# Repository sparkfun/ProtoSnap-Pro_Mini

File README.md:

**_NOTE: This product has been retired from our catalog. This information is made available for those who are curious._**

ProtoSnap Pro-Mini
===================

[
*ProtoSnap Pro Mini (DEV-10889)*](https://www.sparkfun.com/products/10889)

The ProtoSnap is an Arduino-compatible development platform aimed at teach the basics of Arduino programming as efficiently as possible.

Repository Contents
-------------------
* **/Hardware** - All Eagle design files (.brd, .sch)
* **/Production** - Test bed files and production panel files

Product Versions
----------------
* [DEV-10889](https://www.sparkfun.com/products/10889)- Standard ProtoSnap Pro Mini
* [RTL-11053] (https://www.sparkfun.com/products/11053)- Retail version of ProtoSnap Pro Mini

License Information
-------------------
The hardware is released under [Creative Commons ShareAlike 4.0 International](https://creativecommons.org/licenses/by-sa/4.0/).
The code is beerware; if you see me (or any other SparkFun employee) at the local, and you've found our code helpful, please buy us a round!

Distributed as-is; no warranty is given.

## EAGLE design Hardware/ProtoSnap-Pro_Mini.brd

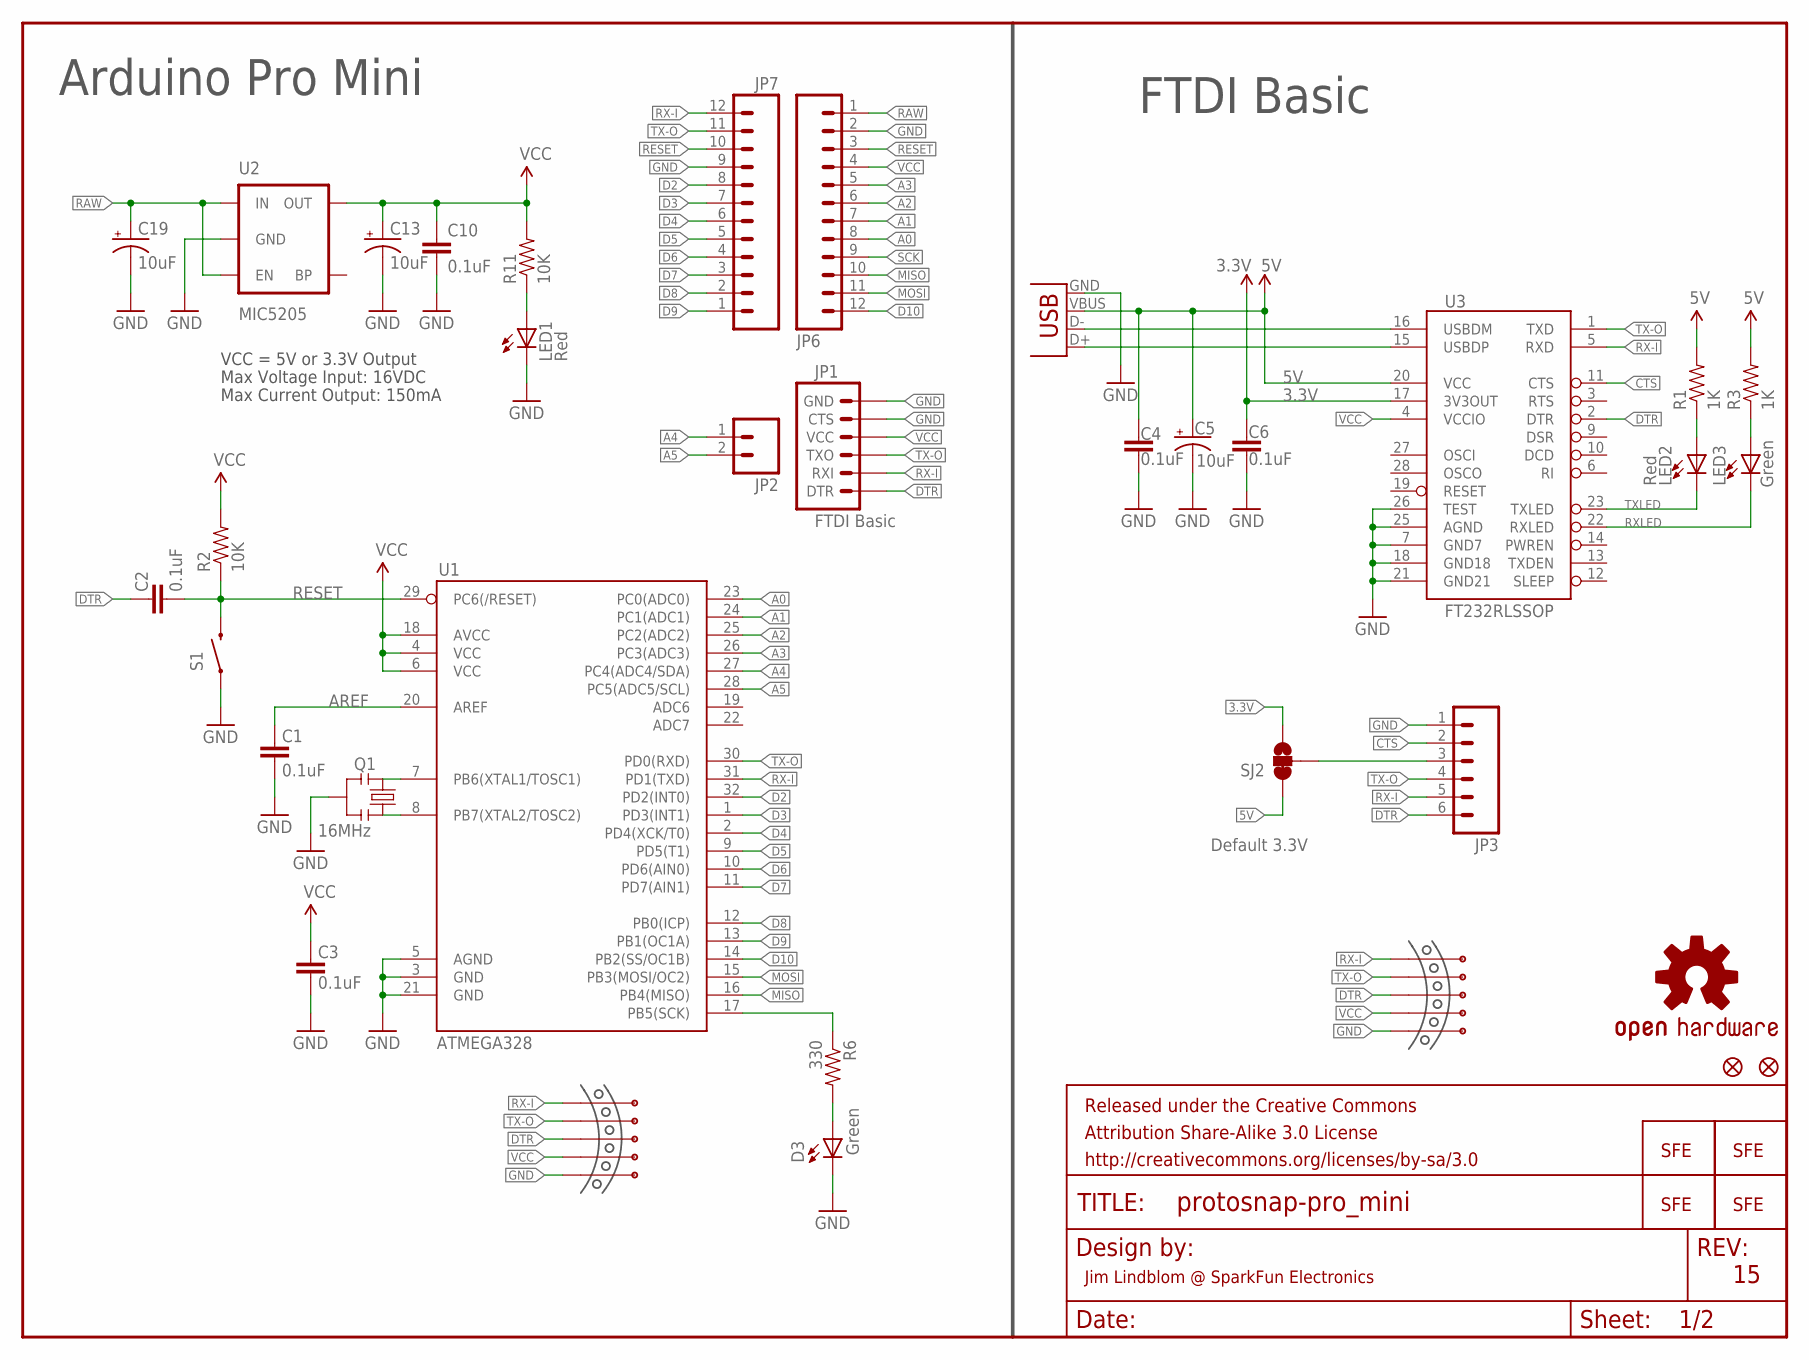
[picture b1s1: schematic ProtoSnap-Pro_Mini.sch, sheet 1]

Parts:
C1, C2, C3, C4, C6, C10: 0.1uF; 0603-CAP
C5, C13, C19: 10uF; EIA3216
D3: Green; 0603-LED-ALT1
FID1, FID2: FIDUCIAL1X2; FIDUCIAL-1X2
FRAME1: FRAME-LETTER; CREATIVE_COMMONS
JP1: FTDI Basic; 1X06
JP2: M02PTH; 1X02
JP3: M06SIP; 1X06
JP4: LOGO-SFENW2; SFE-NEW-WEB
JP6, JP7: M12PTH; 1X12
JP15, JP17: LOGO-SFESK; SFE-LOGO-FLAME
JP18: LOGO-SFENEW; SFE-NEW-WEBLOGO
LED1, LED2: Red; 0603-LED-ALT1
LED3: Green; 0603-LED-ALT1
LOGO1: OSHW-LOGOS; OSHW-LOGO-S
Q1: 16MHz; RESONATOR-SMD-1:1
R1, R3: 1K; 0603-RES
R2, R11: 10K; 0603-RES
R6: 330; 0603-RES
S1: SWITCH-MOMENTARY-2SMD-ALT01; TACTILE-SWITCH-SMD-ALT01
SJ2: SOLDERJUMPER_2WAYS; SJ_3
U1: ATMEGA328; TQFP32-08
U2: MIC5205; SOT23-5
U3: FT232RLSSOP; SSOP28DB
U$22, U$23: MOUSE-BITE-5
X2: USB-SMD-NS; USB-MINIB-NOSTOP

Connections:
3.3V: C6.1, SJ2.3, U3.17 (3V3OUT)
5V: C4.1, C5.A (+), R1.2, R3.2, SJ2.1, U3.20 (VCC), X2.VBUS
A0: JP6.8, U1.23 (PC0(ADC0)); also elsewhere on the board
A1: JP6.7, U1.24 (PC1(ADC1))
A2: JP6.6, U1.25 (PC2(ADC2))
A3: JP6.5, U1.26 (PC3(ADC3))
A4: JP2.1, U1.27 (PC4(ADC4/SDA))
A5: JP2.2, U1.28 (PC5(ADC5/SCL))
AREF: C1.2, U1.20 (AREF)
CTS: JP3.2, U3.11 (CTS)
D2: JP7.8, U1.32 (PD2(INT0)); also elsewhere on the board
D3: JP7.7, U1.1 (PD3(INT1)); also elsewhere on the board
D4: JP7.6, U1.2 (PD4(XCK/T0))
D5: JP7.5, U1.9 (PD5(T1)); also elsewhere on the board
D6: JP7.4, U1.10 (PD6(AIN0)); also elsewhere on the board
D7: JP7.3, U1.11 (PD7(AIN1)); also elsewhere on the board
D8: JP7.2, U1.12 (PB0(ICP))
D9: JP7.1, U1.13 (PB1(OC1A))
D10: JP6.12, U1.14 (PB2(SS/OC1B))
DTR: C2.2, JP1.1 (DTR), JP3.6, U3.2 (DTR), U$22.P$3, U$23.P$3
GND: C1.1, C3.1, C4.2, C5.C (-), C6.2, C10.2, C13.C (-), C19.C (-), D3.C, JP1.5 (CTS), JP1.6 (GND), JP3.1, JP6.2, JP7.9, LED1.C, Q1.2, S1.1, S1.2 (1), U1.3 (GND), U1.5 (AGND), U1.21 (GND), U2.2 (GND), U3.7 (GND7), U3.18 (GND18), U3.21 (GND21), U3.25 (AGND), U3.26 (TEST), U$22.P$5, U$23.P$5, X2.GND; also elsewhere on the board
MISO: JP6.10, U1.16 (PB4(MISO))
MOSI: JP6.11, U1.15 (PB3(MOSI/OC2))
unnamed: Q1.1, U1.8 (PB7(XTAL2/TOSC2))
unnamed: Q1.3, U1.7 (PB6(XTAL1/TOSC1))
unnamed: LED2.A, R1.1
unnamed: LED3.A, R3.1
unnamed: D3.A, R6.2
unnamed: LED1.A, R11.1
RAW: C19.A (+), JP6.1, U2.1 (IN), U2.3 (EN)
RESET: C2.1, JP6.3, JP7.10, R2.1, S1.3 (2), S1.4 (2), U1.29 (PC6(/RESET))
RX-I: JP1.2 (RXI), JP3.5, JP7.12, U1.31 (PD1(TXD)), U3.5 (RXD), U$22.P$1, U$23.P$1
RXLED: LED3.C, U3.22 (RXLED)
SCK: JP6.9, R6.1, U1.17 (PB5(SCK))
TX-O: JP1.3 (TXO), JP3.4, JP7.11, U1.30 (PD0(RXD)), U3.1 (TXD), U$22.P$2, U$23.P$2
TXLED: LED2.C, U3.23 (TXLED)
USB_D+: U3.15 (USBDP), X2.D+
USB_D-: U3.16 (USBDM), X2.D-
VCC: C3.2, C10.1, C13.A (+), JP1.4 (VCC), JP3.3, JP6.4, R2.2, R11.2, SJ2.2, U1.4 (VCC), U1.6 (VCC), U1.18 (AVCC), U2.5 (OUT), U3.4 (VCCIO), U$22.P$4, U$23.P$4; also elsewhere on the board

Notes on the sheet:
Max Voltage Input: 16VDC
Max Current Output: 150mA
VCC = 5V or 3.3V Output
Jim Lindblom @ SparkFun Electronics
Arduino Pro Mini
Default 3.3V
FTDI Basic

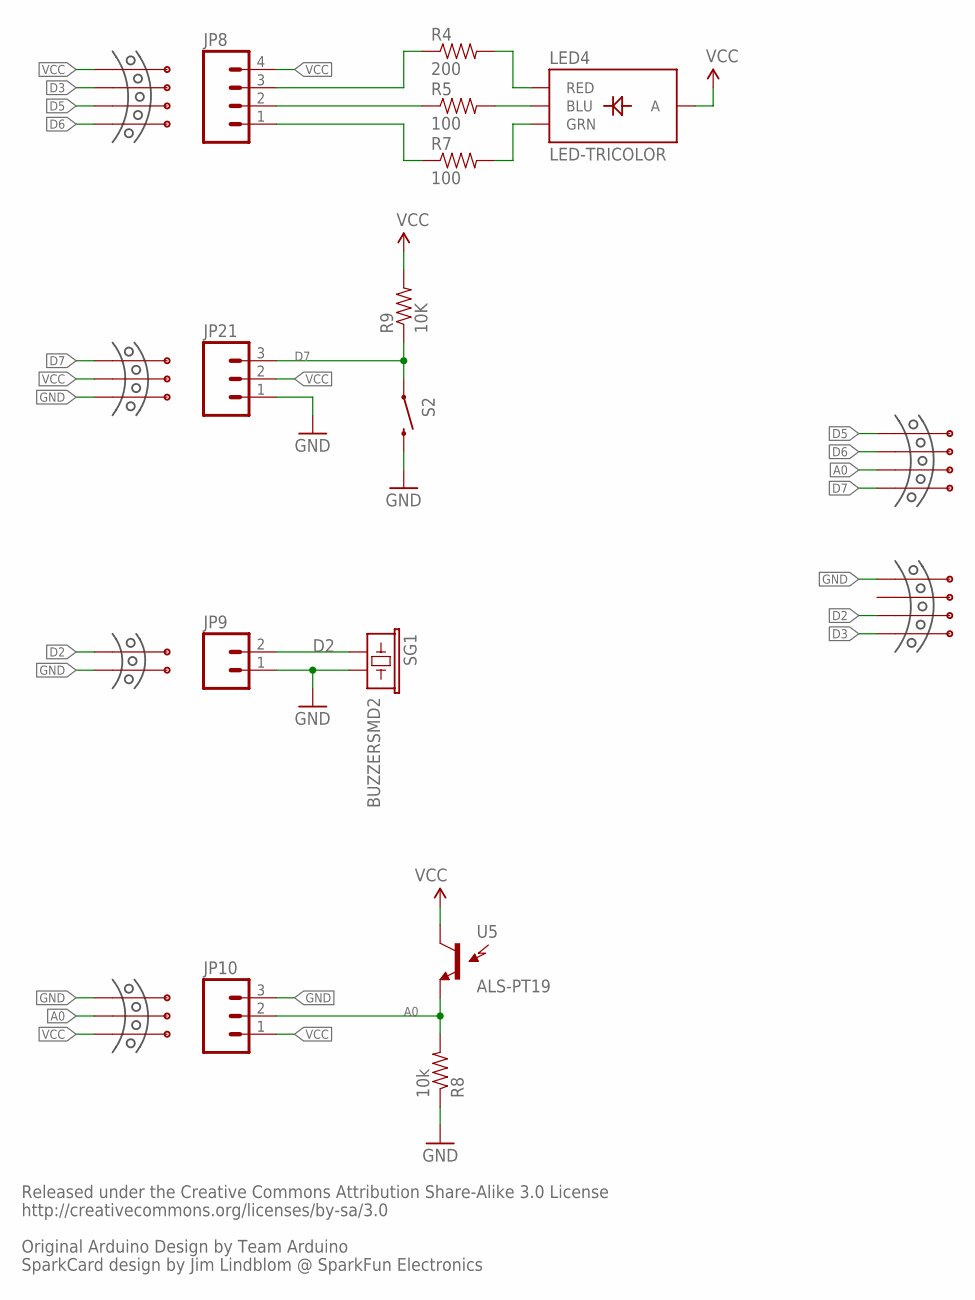
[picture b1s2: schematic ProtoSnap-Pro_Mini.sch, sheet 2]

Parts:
JP8: M04PTH; 1X04
JP9: M02PTH; 1X02
JP10, JP21: M03PTH; 1X03
LED4: LED-TRICOLOR; LED-TRICOLOR-SMD
R4: 200; 0603-RES
R5, R7: 100; 0603-RES
R8: 10k; 0603-RES
R9: 10K; 0603-RES
S2: SWITCH-MOMENTARY-2SMD-ALT01; TACTILE-SWITCH-SMD-ALT01
SG1: BUZZERSMD2; BUZZER-CCV
U5: ALS-PT19
U$2, U$9: MOUSE-BITE-3
U$7: MOUSE-BITE-2
U$8, U$13, U$14: MOUSE-BITE-4

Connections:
A0: JP10.2, R8.2, U5.E (E1), U$9.P$2, U$13.P$3; also elsewhere on the board
D2: JP9.2, SG1.+ (1), U$7.P$1, U$14.P$3; also elsewhere on the board
D3: JP8.3, R4.1, U$8.P$2, U$14.P$4; also elsewhere on the board
D5: JP8.1, R7.1, U$8.P$3, U$13.P$1; also elsewhere on the board
D6: JP8.2, R5.1, U$8.P$4, U$13.P$2; also elsewhere on the board
D7: JP21.3, R9.1, S2.1, S2.2 (1), U$2.P$3, U$13.P$4; also elsewhere on the board
GND: JP9.1, JP10.3, JP21.1, R8.1, S2.3 (2), S2.4 (2), SG1.- (2), U$2.P$1, U$7.P$2, U$9.P$3, U$14.P$1; also elsewhere on the board
unnamed: LED4.R (RED), R4.2
unnamed: LED4.B (BLU), R5.2
unnamed: LED4.G (GRN), R7.2
VCC: JP8.4, JP10.1, JP21.2, LED4.A, R9.2, U5.C (C1), U$2.P$2, U$8.P$1, U$9.P$1; also elsewhere on the board

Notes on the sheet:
Released under the Creative Commons Attribution Share-Alike 3.0 License
http://creativecommons.org/licenses/by-sa/3.0
Original Arduino Design by Team Arduino
SparkCard design by Jim Lindblom @ SparkFun Electronics

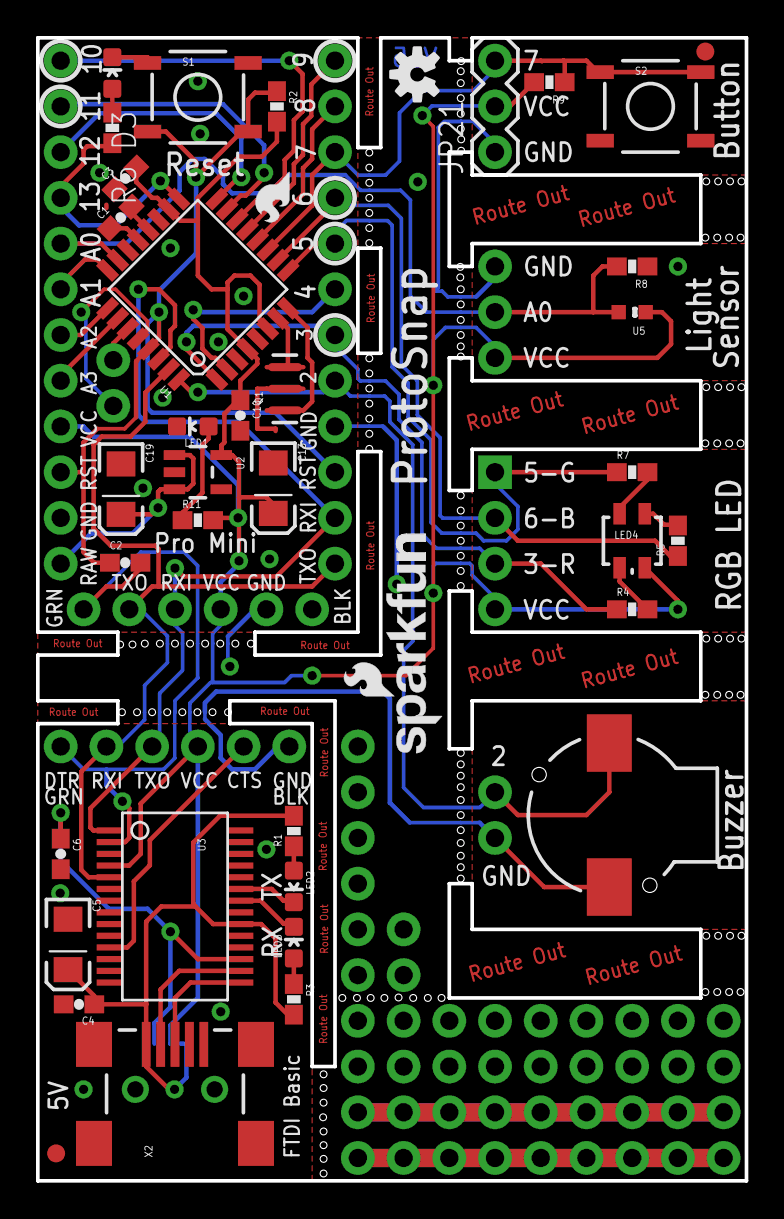
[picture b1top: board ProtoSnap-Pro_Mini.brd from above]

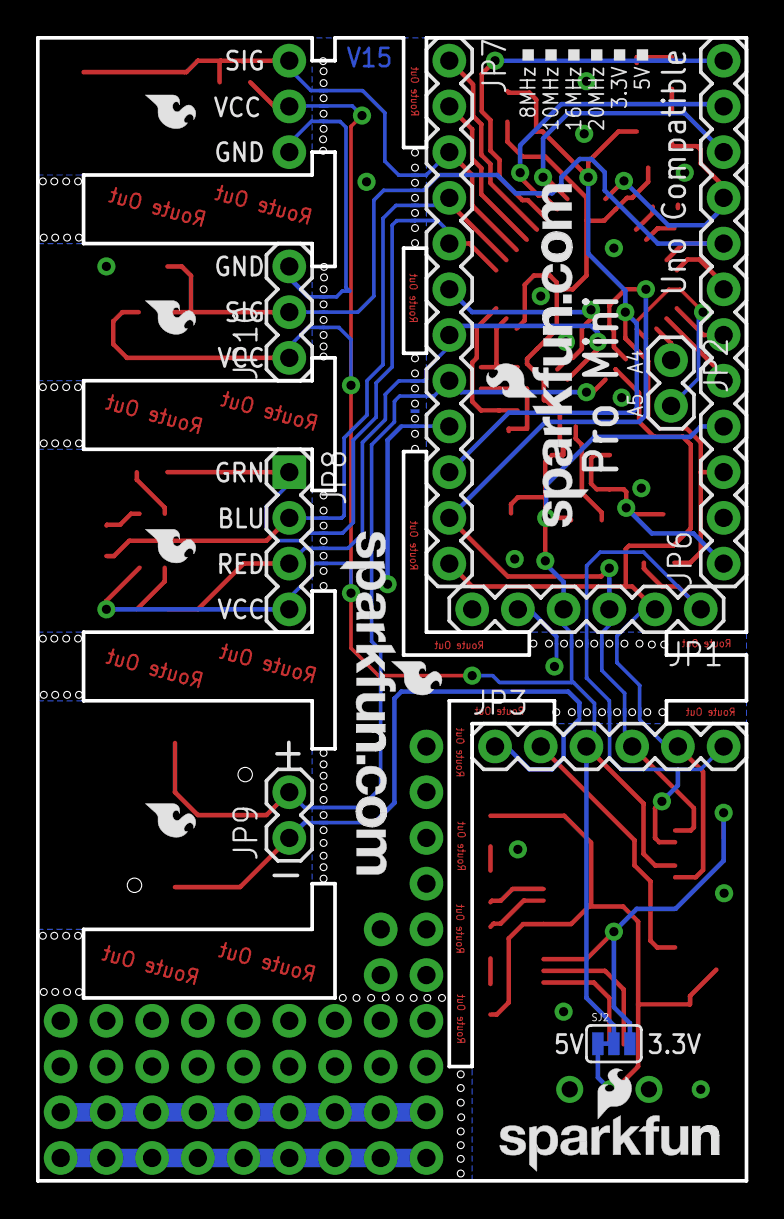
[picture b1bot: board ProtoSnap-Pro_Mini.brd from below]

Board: 2 copper layers, 39.4 x 63.5 mm, 66 parts (17 on the bottom side), 42 nets.

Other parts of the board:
JP5, JP11, JP13, JP14: LOGO-SFESK; SFE-LOGO-FLAME
JP12: LOGO-SFENW2; SFE-NEW-WEB
U$1: LOGO-SFESK; SFE-LOGO-FLAME
U$11: LOGO-SFENEW; SFE-NEW-WEBLOGO

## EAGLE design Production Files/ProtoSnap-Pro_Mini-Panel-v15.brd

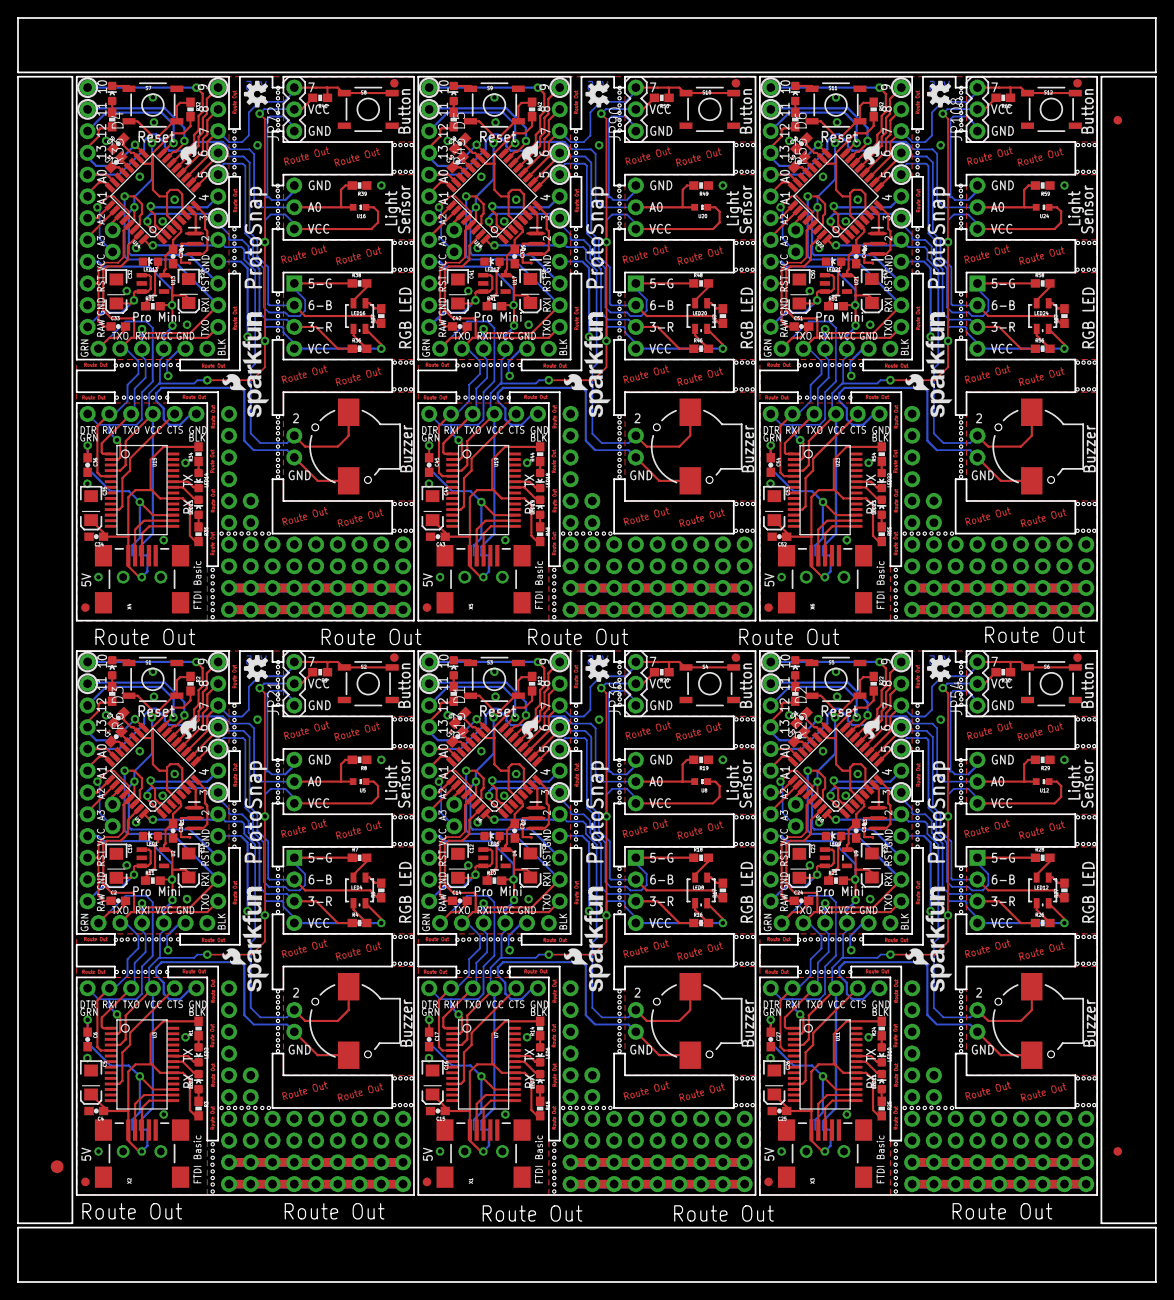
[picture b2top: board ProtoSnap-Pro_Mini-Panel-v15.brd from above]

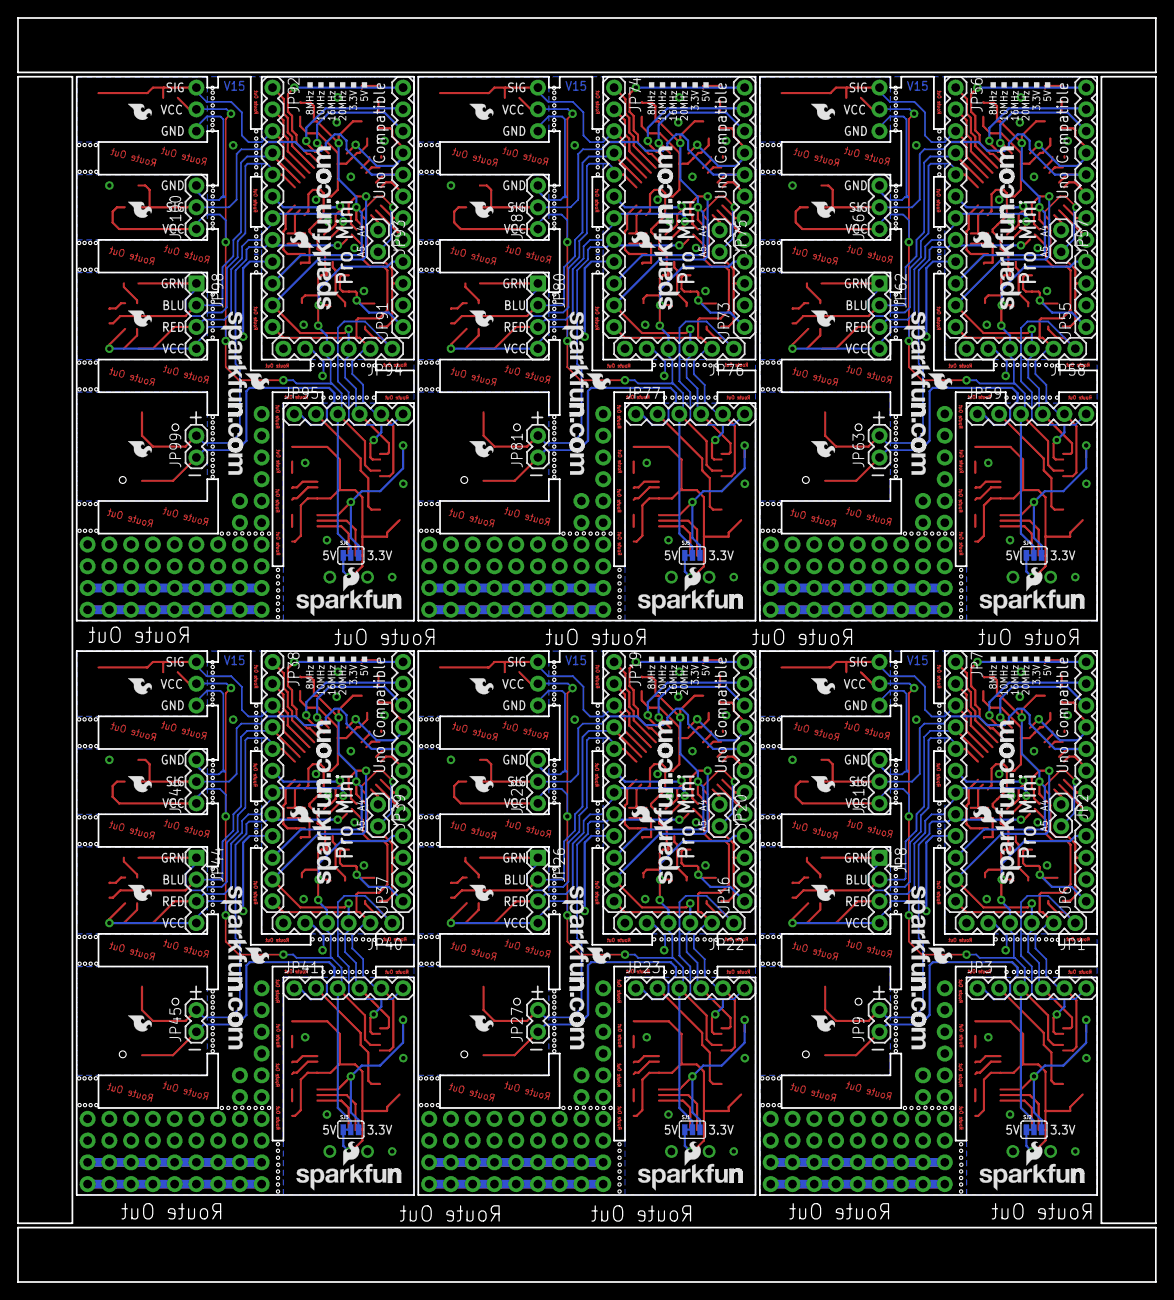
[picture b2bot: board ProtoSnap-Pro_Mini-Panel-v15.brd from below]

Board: 2 copper layers, 132.8 x 147.6 mm, 393 parts (102 on the bottom side), 252 nets.

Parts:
C1, C2, C3, C4, C6, C7, C9, C10, C11, C14, C15, C17, C18, C21, C22, C24, C25, C27, C28, C30, C31, C33, C34, C36, C37, C39, C40, C42, C43, C45, C46, C48, C49, C51, C52, C54: 0.1uF; 0603-CAP
C5, C8, C12, C13, C16, C19, C20, C23, C26, C29, C32, C35, C38, C41, C44, C47, C50, C53: 10uF; EIA3216
D1, D2, D3, D4, D5, D6: Green; 0603-LED-ALT1
E$1: FIDUCIAL-1.5X3
E$3, E$4: FIDUCIAL-1X2
FID1, FID2, FID3, FID4, FID5, FID6, FID7, FID8, FID9, FID10, FID11, FID12: FIDUCIAL1X2; FIDUCIAL-1X2
JP1, JP22, JP40, JP58, JP76, JP94: FTDI Basic; 1X06
JP2, JP9, JP20, JP27, JP39, JP45, JP57, JP63, JP75, JP81, JP93, JP99: 1X02
JP3, JP23, JP41, JP59, JP77, JP95: 1X06
JP4, JP12, JP24, JP33, JP42, JP51, JP60, JP69, JP78, JP87, JP96, JP105: LOGO-SFENW2; SFE-NEW-WEB
JP5, JP11, JP13, JP14, JP15, JP17, JP25, JP29, JP30, JP31, JP32, JP34, JP43, JP47, JP48, JP49, JP50, JP52, JP61, JP65, JP66, JP67, JP68, JP70, JP79, JP83, JP84, JP85, JP86, JP88, JP97, JP101, JP102, JP103, JP104, JP106: LOGO-SFESK; SFE-LOGO-FLAME
JP6, JP7, JP16, JP19, JP37, JP38, JP55, JP56, JP73, JP74, JP91, JP92: 1X12
JP8, JP26, JP44, JP62, JP80, JP98: 1X04
JP10, JP21, JP28, JP36, JP46, JP54, JP64, JP72, JP82, JP90, JP100, JP108: 1X03
JP18, JP35, JP53, JP71, JP89, JP107: LOGO-SFENEW; SFE-NEW-WEBLOGO
LED1, LED2, LED5, LED6, LED9, LED10, LED13, LED14, LED17, LED18, LED21, LED22: Red; 0603-LED-ALT1
LED3, LED7, LED11, LED15, LED19, LED23: Green; 0603-LED-ALT1
LED4, LED8, LED12, LED16, LED20, LED24: LED-TRICOLOR; LED-TRICOLOR-SMD
LOGO1, LOGO2, LOGO3, LOGO4, LOGO5, LOGO6: OSHW-LOGOS; OSHW-LOGO-S
Q1, Q2, Q3, Q4, Q5, Q6: 16MHz; RESONATOR-SMD-1:1
R1, R3, R14, R15, R24, R25, R34, R35, R44, R45, R54, R55: 1K; 0603-RES
R2, R9, R10, R11, R12, R20, R21, R22, R30, R31, R32, R40, R41, R42, R50, R51, R52, R60: 10K; 0603-RES
R4, R16, R26, R36, R46, R56: 200; 0603-RES
R5, R7, R17, R18, R27, R28, R37, R38, R47, R48, R57, R58: 100; 0603-RES
R6, R13, R23, R33, R43, R53: 330; 0603-RES
R8, R19, R29, R39, R49, R59: 10k; 0603-RES
S1, S2, S3, S4, S5, S6, S7, S8, S9, S10, S11, S12: TACTILE-SWITCH-SMD-ALT01
SG1, SG2, SG3, SG4, SG5, SG6: BUZZERSMD2; BUZZER-CCV
SJ1, SJ2, SJ3, SJ4, SJ5, SJ6: SJ_3
U1, U6, U10, U14, U18, U22: ATMEGA328; TQFP32-08
U2, U4, U9, U13, U17, U21: MIC5205; SOT23-5
U3, U7, U11, U15, U19, U23: FT232RLSSOP; SSOP28DB
U5, U8, U12, U16, U20, U24: ALS-PT19
U$1, U$4, U$20, U$32, U$42, U$52: LOGO-SFESK; SFE-LOGO-FLAME
U$2, U$9, U$16, U$18, U$28, U$30, U$38, U$40, U$48, U$50, U$58, U$60: MOUSE-BITE-3
U$3, U$11, U$19, U$31, U$41, U$51: LOGO-SFENEW; SFE-NEW-WEBLOGO
U$5, U$7, U$21, U$33, U$43, U$53: MOUSE-BITE-2
U$6, U$10, U$22, U$23, U$24, U$25, U$34, U$35, U$44, U$45, U$54, U$55: MOUSE-BITE-5
U$8, U$12, U$13, U$14, U$15, U$17, U$26, U$27, U$29, U$36, U$37, U$39, U$46, U$47, U$49, U$56, U$57, U$59: MOUSE-BITE-4
X1, X2, X3, X4, X5, X6: USB-SMD-NS; USB-MINIB-NOSTOP

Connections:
3.3V: C6.1, SJ2.3, U3.17
3.3V1: C17.1, SJ1.3, U7.17
3.3V2: C27.1, SJ3.3, U11.17
3.3V3: C36.1, SJ4.3, U15.17
3.3V4: C45.1, SJ5.3, U19.17
3.3V5: C54.1, SJ6.3, U23.17
5V: C4.1, C5.A, R1.2, R3.2, SJ2.1, U3.20, X2.VBUS
5V1: C15.1, C16.A, R14.2, R15.2, SJ1.1, U7.20, X1.VBUS
5V2: C25.1, C26.A, R24.2, R25.2, SJ3.1, U11.20, X3.VBUS
5V3: C34.1, C35.A, R34.2, R35.2, SJ4.1, U15.20, X4.VBUS
5V4: C43.1, C44.A, R44.2, R45.2, SJ5.1, U19.20, X5.VBUS
5V5: C52.1, C53.A, R54.2, R55.2, SJ6.1, U23.20, X6.VBUS
A0: JP6.8, JP10.2, R8.2, U1.23, U5.E, U$9.P$2, U$13.P$3
A1: JP6.7, U1.24
A2: JP6.6, U1.25
A3: JP6.5, U1.26
A4: JP2.1, U1.27
A5: JP2.2, U1.28
A6: JP20.2, U6.28
A7: JP20.1, U6.27
A8: JP16.5, U6.26
A9: JP16.6, U6.25
A10: JP16.7, U6.24
A11: JP16.8, JP28.2, R19.2, U6.23, U8.E, U$15.P$3, U$16.P$2
A12: JP39.2, U10.28
A13: JP39.1, U10.27
A14: JP37.5, U10.26
A15: JP37.6, U10.25
A16: JP37.7, U10.24
A17: JP37.8, JP46.2, R29.2, U10.23, U12.E, U$27.P$3, U$28.P$2
A18: JP57.2, U14.28
A19: JP57.1, U14.27
A20: JP55.5, U14.26
A21: JP55.6, U14.25
A22: JP55.7, U14.24
A23: JP55.8, JP64.2, R39.2, U14.23, U16.E, U$37.P$3, U$38.P$2
A24: JP75.2, U18.28
A25: JP75.1, U18.27
A26: JP73.5, U18.26
A27: JP73.6, U18.25
A28: JP73.7, U18.24
A29: JP73.8, JP82.2, R49.2, U18.23, U20.E, U$47.P$3, U$48.P$2
A30: JP93.2, U22.28
A31: JP93.1, U22.27
A32: JP91.5, U22.26
A33: JP91.6, U22.25
A34: JP91.7, U22.24
A35: JP91.8, JP100.2, R59.2, U22.23, U24.E, U$57.P$3, U$58.P$2
AREF: C1.2, U1.20
AREF1: C11.2, U6.20
AREF2: C22.2, U10.20
AREF3: C31.2, U14.20
AREF4: C40.2, U18.20
AREF5: C49.2, U22.20
CTS: JP3.2, U3.11
CTS1: JP23.2, U7.11
CTS2: JP41.2, U11.11
CTS3: JP59.2, U15.11
CTS4: JP77.2, U19.11
CTS5: JP95.2, U23.11
D1: JP19.1, U6.13
D2: JP7.8, JP9.2, SG1.+, U1.32, U$7.P$1, U$14.P$3
D3: JP7.7, JP8.3, R4.1, U1.1, U$8.P$2, U$14.P$4
D4: JP7.6, U1.2
D5: JP7.5, JP8.1, R7.1, U1.9, U$8.P$3, U$13.P$1
D6: JP7.4, JP8.2, R5.1, U1.10, U$8.P$4, U$13.P$2
D7: JP7.3, JP21.3, R9.1, S2.1, S2.2, U1.11, U$2.P$3, U$13.P$4
D8: JP7.2, U1.12
D9: JP7.1, U1.13
D10: JP6.12, U1.14
D11: JP19.2, U6.12
D12: JP19.8, JP27.2, SG2.+, U6.32, U$5.P$1, U$17.P$3
D13: JP19.7, JP26.3, R16.1, U6.1, U$12.P$2, U$17.P$4
D14: JP19.6, U6.2
D15: JP19.5, JP26.1, R18.1, U6.9, U$12.P$3, U$15.P$1
D16: JP19.4, JP26.2, R17.1, U6.10, U$12.P$4, U$15.P$2
D17: JP19.3, JP36.3, R20.1, S4.1, S4.2, U6.11, U$15.P$4, U$18.P$3
D18: JP16.12, U6.14
D19: JP38.1, U10.13
D20: JP38.2, U10.12
D21: JP38.8, JP45.2, SG3.+, U10.32, U$21.P$1, U$29.P$3
D22: JP38.7, JP44.3, R26.1, U10.1, U$26.P$2, U$29.P$4
D23: JP38.6, U10.2
D24: JP38.5, JP44.1, R28.1, U10.9, U$26.P$3, U$27.P$1
D25: JP38.4, JP44.2, R27.1, U10.10, U$26.P$4, U$27.P$2
D26: JP38.3, JP54.3, R30.1, S6.1, S6.2, U10.11, U$27.P$4, U$30.P$3
D27: JP37.12, U10.14
D28: JP56.1, U14.13
D29: JP56.2, U14.12
D30: JP56.8, JP63.2, SG4.+, U14.32, U$33.P$1, U$39.P$3
D31: JP56.7, JP62.3, R36.1, U14.1, U$36.P$2, U$39.P$4
D32: JP56.6, U14.2
D33: JP56.5, JP62.1, R38.1, U14.9, U$36.P$3, U$37.P$1
D34: JP56.4, JP62.2, R37.1, U14.10, U$36.P$4, U$37.P$2
D35: JP56.3, JP72.3, R40.1, S8.1, S8.2, U14.11, U$37.P$4, U$40.P$3
D36: JP55.12, U14.14
D37: JP74.1, U18.13
D38: JP74.2, U18.12
D39: JP74.8, JP81.2, SG5.+, U18.32, U$43.P$1, U$49.P$3
D40: JP74.7, JP80.3, R46.1, U18.1, U$46.P$2, U$49.P$4
D41: JP74.6, U18.2
D42: JP74.5, JP80.1, R48.1, U18.9, U$46.P$3, U$47.P$1
D43: JP74.4, JP80.2, R47.1, U18.10, U$46.P$4, U$47.P$2
D44: JP74.3, JP90.3, R50.1, S10.1, S10.2, U18.11, U$47.P$4, U$50.P$3
D45: JP73.12, U18.14
D46: JP92.1, U22.13
D47: JP92.2, U22.12
D48: JP92.8, JP99.2, SG6.+, U22.32, U$53.P$1, U$59.P$3
D49: JP92.7, JP98.3, R56.1, U22.1, U$56.P$2, U$59.P$4
D50: JP92.6, U22.2
D51: JP92.5, JP98.1, R58.1, U22.9, U$56.P$3, U$57.P$1
D52: JP92.4, JP98.2, R57.1, U22.10, U$56.P$4, U$57.P$2
D53: JP92.3, JP108.3, R60.1, S12.1, S12.2, U22.11, U$57.P$4, U$60.P$3
D54: JP91.12, U22.14
DTR: C2.2, JP1.1, JP3.6, U3.2, U$22.P$3, U$23.P$3
DTR1: C14.2, JP22.1, JP23.6, U7.2, U$6.P$3, U$10.P$3
DTR2: C24.2, JP40.1, JP41.6, U11.2, U$24.P$3, U$25.P$3
DTR3: C33.2, JP58.1, JP59.6, U15.2, U$34.P$3, U$35.P$3
DTR4: C42.2, JP76.1, JP77.6, U19.2, U$44.P$3, U$45.P$3
DTR5: C51.2, JP94.1, JP95.6, U23.2, U$54.P$3, U$55.P$3
GND: C1.1, C3.1, C4.2, C5.C, C6.2, C10.2, C13.C, C19.C, D3.C, JP1.5, JP1.6, JP3.1, JP6.2, JP7.9, JP9.1, JP10.3, JP21.1, LED1.C, Q1.2, R8.1, S1.1, S1.2, S2.3, S2.4, SG1.-, U1.3, U1.5, U1.21, U2.2, U3.7, U3.18, U3.21, U3.25, U3.26, U$2.P$1, U$7.P$2, U$9.P$3, U$14.P$1, U$22.P$5, U$23.P$5, X2.GND
GND1: C7.2, C8.C, C9.1, C11.1, C12.C, C15.2, C16.C, C17.2, D1.C, JP16.2, JP19.9, JP22.5, JP22.6, JP23.1, JP27.1, JP28.3, JP36.1, LED5.C, Q2.2, R19.1, S3.1, S3.2, S4.3, S4.4, SG2.-, U4.2, U6.3, U6.5, U6.21, U7.7, U7.18, U7.21, U7.25, U7.26, U$5.P$2, U$6.P$5, U$10.P$5, U$16.P$3, U$17.P$1, U$18.P$1, X1.GND
GND2: C18.2, C20.C, C21.1, C22.1, C23.C, C25.2, C26.C, C27.2, D2.C, JP37.2, JP38.9, JP40.5, JP40.6, JP41.1, JP45.1, JP46.3, JP54.1, LED9.C, Q3.2, R29.1, S5.1, S5.2, S6.3, S6.4, SG3.-, U9.2, U10.3, U10.5, U10.21, U11.7, U11.18, U11.21, U11.25, U11.26, U$21.P$2, U$24.P$5, U$25.P$5, U$28.P$3, U$29.P$1, U$30.P$1, X3.GND
GND3: C28.2, C29.C, C30.1, C31.1, C32.C, C34.2, C35.C, C36.2, D4.C, JP55.2, JP56.9, JP58.5, JP58.6, JP59.1, JP63.1, JP64.3, JP72.1, LED13.C, Q4.2, R39.1, S7.1, S7.2, S8.3, S8.4, SG4.-, U13.2, U14.3, U14.5, U14.21, U15.7, U15.18, U15.21, U15.25, U15.26, U$33.P$2, U$34.P$5, U$35.P$5, U$38.P$3, U$39.P$1, U$40.P$1, X4.GND
GND4: C37.2, C38.C, C39.1, C40.1, C41.C, C43.2, C44.C, C45.2, D5.C, JP73.2, JP74.9, JP76.5, JP76.6, JP77.1, JP81.1, JP82.3, JP90.1, LED17.C, Q5.2, R49.1, S9.1, S9.2, S10.3, S10.4, SG5.-, U17.2, U18.3, U18.5, U18.21, U19.7, U19.18, U19.21, U19.25, U19.26, U$43.P$2, U$44.P$5, U$45.P$5, U$48.P$3, U$49.P$1, U$50.P$1, X5.GND
GND5: C46.2, C47.C, C48.1, C49.1, C50.C, C52.2, C53.C, C54.2, D6.C, JP91.2, JP92.9, JP94.5, JP94.6, JP95.1, JP99.1, JP100.3, JP108.1, LED21.C, Q6.2, R59.1, S11.1, S11.2, S12.3, S12.4, SG6.-, U21.2, U22.3, U22.5, U22.21, U23.7, U23.18, U23.21, U23.25, U23.26, U$53.P$2, U$54.P$5, U$55.P$5, U$58.P$3, U$59.P$1, U$60.P$1, X6.GND
MISO: JP6.10, U1.16
MISO1: JP16.10, U6.16
MISO2: JP37.10, U10.16
MISO3: JP55.10, U14.16
MISO4: JP73.10, U18.16
MISO5: JP91.10, U22.16
MOSI: JP6.11, U1.15
MOSI1: JP16.11, U6.15
MOSI2: JP37.11, U10.15
MOSI3: JP55.11, U14.15
MOSI4: JP73.11, U18.15
MOSI5: JP91.11, U22.15
unnamed: Q1.1, U1.8
unnamed: Q1.3, U1.7
unnamed: LED2.A, R1.1
unnamed: LED3.A, R3.1
unnamed: LED4.R, R4.2
unnamed: D3.A, R6.2
unnamed: LED4.B, R5.2
unnamed: LED4.G, R7.2
unnamed: LED5.A, R10.1
unnamed: D1.A, R13.2
unnamed: Q2.1, U6.8
unnamed: Q2.3, U6.7
unnamed: LED1.A, R11.1
unnamed: LED6.A, R14.1
unnamed: LED7.A, R15.1
unnamed: LED8.R, R16.2
unnamed: LED8.B, R17.2
unnamed: LED8.G, R18.2
unnamed: LED9.A, R21.1
unnamed: D2.A, R23.2
unnamed: Q3.1, U10.8
unnamed: Q3.3, U10.7
unnamed: LED10.A, R24.1
unnamed: LED11.A, R25.1
unnamed: LED12.R, R26.2
unnamed: LED12.B, R27.2
unnamed: LED12.G, R28.2
unnamed: LED13.A, R31.1
unnamed: D4.A, R33.2
unnamed: Q4.1, U14.8
unnamed: Q4.3, U14.7
unnamed: LED14.A, R34.1
unnamed: LED15.A, R35.1
unnamed: LED16.R, R36.2
unnamed: LED16.B, R37.2
unnamed: LED16.G, R38.2
unnamed: LED17.A, R41.1
unnamed: D5.A, R43.2
unnamed: Q5.1, U18.8
unnamed: Q5.3, U18.7
unnamed: LED18.A, R44.1
unnamed: LED19.A, R45.1
unnamed: LED20.R, R46.2
unnamed: LED20.B, R47.2
unnamed: LED20.G, R48.2
unnamed: LED21.A, R51.1
unnamed: D6.A, R53.2
unnamed: Q6.1, U22.8
unnamed: Q6.3, U22.7
unnamed: LED22.A, R54.1
unnamed: LED23.A, R55.1
unnamed: LED24.R, R56.2
unnamed: LED24.B, R57.2
unnamed: LED24.G, R58.2
RAW: C19.A, JP6.1, U2.1, U2.3
RAW1: C12.A, JP16.1, U4.1, U4.3
RAW2: C23.A, JP37.1, U9.1, U9.3
RAW3: C32.A, JP55.1, U13.1, U13.3
RAW4: C41.A, JP73.1, U17.1, U17.3
RAW5: C50.A, JP91.1, U21.1, U21.3
RESET: C2.1, JP6.3, JP7.10, R2.1, S1.3, S1.4, U1.29
RESET1: C14.1, JP16.3, JP19.10, R12.1, S3.3, S3.4, U6.29
RESET2: C24.1, JP37.3, JP38.10, R22.1, S5.3, S5.4, U10.29
RESET3: C33.1, JP55.3, JP56.10, R32.1, S7.3, S7.4, U14.29
RESET4: C42.1, JP73.3, JP74.10, R42.1, S9.3, S9.4, U18.29
RESET5: C51.1, JP91.3, JP92.10, R52.1, S11.3, S11.4, U22.29
RX-I: JP1.2, JP3.5, JP7.12, U1.31, U3.5, U$22.P$1, U$23.P$1
RX-I1: JP19.12, JP22.2, JP23.5, U6.31, U7.5, U$6.P$1, U$10.P$1
RX-I2: JP38.12, JP40.2, JP41.5, U10.31, U11.5, U$24.P$1, U$25.P$1
RX-I3: JP56.12, JP58.2, JP59.5, U14.31, U15.5, U$34.P$1, U$35.P$1
RX-I4: JP74.12, JP76.2, JP77.5, U18.31, U19.5, U$44.P$1, U$45.P$1
RX-I5: JP92.12, JP94.2, JP95.5, U22.31, U23.5, U$54.P$1, U$55.P$1
RXLED: LED3.C, U3.22
RXLED1: LED7.C, U7.22
RXLED2: LED11.C, U11.22
RXLED3: LED15.C, U15.22
RXLED4: LED19.C, U19.22
RXLED5: LED23.C, U23.22
SCK: JP6.9, R6.1, U1.17
SCK1: JP16.9, R13.1, U6.17
SCK2: JP37.9, R23.1, U10.17
SCK3: JP55.9, R33.1, U14.17
SCK4: JP73.9, R43.1, U18.17
SCK5: JP91.9, R53.1, U22.17
TX-O: JP1.3, JP3.4, JP7.11, U1.30, U3.1, U$22.P$2, U$23.P$2
TX-O1: JP19.11, JP22.3, JP23.4, U6.30, U7.1, U$6.P$2, U$10.P$2
TX-O2: JP38.11, JP40.3, JP41.4, U10.30, U11.1, U$24.P$2, U$25.P$2
TX-O3: JP56.11, JP58.3, JP59.4, U14.30, U15.1, U$34.P$2, U$35.P$2
TX-O4: JP74.11, JP76.3, JP77.4, U18.30, U19.1, U$44.P$2, U$45.P$2
TX-O5: JP92.11, JP94.3, JP95.4, U22.30, U23.1, U$54.P$2, U$55.P$2
TXLED: LED2.C, U3.23
TXLED1: LED6.C, U7.23
TXLED2: LED10.C, U11.23
TXLED3: LED14.C, U15.23
TXLED4: LED18.C, U19.23
TXLED5: LED22.C, U23.23
USB_D+: U3.15, X2.D+
USB_D+1: U7.15, X1.D+
USB_D+2: U11.15, X3.D+
USB_D+3: U15.15, X4.D+
USB_D+4: U19.15, X5.D+
USB_D+5: U23.15, X6.D+
USB_D-: U3.16, X2.D-
USB_D-1: U7.16, X1.D-
USB_D-2: U11.16, X3.D-
USB_D-3: U15.16, X4.D-
USB_D-4: U19.16, X5.D-
USB_D-5: U23.16, X6.D-
VCC: C3.2, C10.1, C13.A, JP1.4, JP3.3, JP6.4, JP8.4, JP10.1, JP21.2, LED4.A, R2.2, R9.2, R11.2, SJ2.2, U1.4, U1.6, U1.18, U2.5, U3.4, U5.C, U$2.P$2, U$8.P$1, U$9.P$1, U$22.P$4, U$23.P$4
VCC1: C7.1, C8.A, C9.2, JP16.4, JP22.4, JP23.3, JP26.4, JP28.1, JP36.2, LED8.A, R10.2, R12.2, R20.2, SJ1.2, U4.5, U6.4, U6.6, U6.18, U7.4, U8.C, U$6.P$4, U$10.P$4, U$12.P$1, U$16.P$1, U$18.P$2
VCC2: C18.1, C20.A, C21.2, JP37.4, JP40.4, JP41.3, JP44.4, JP46.1, JP54.2, LED12.A, R21.2, R22.2, R30.2, SJ3.2, U9.5, U10.4, U10.6, U10.18, U11.4, U12.C, U$24.P$4, U$25.P$4, U$26.P$1, U$28.P$1, U$30.P$2
VCC3: C28.1, C29.A, C30.2, JP55.4, JP58.4, JP59.3, JP62.4, JP64.1, JP72.2, LED16.A, R31.2, R32.2, R40.2, SJ4.2, U13.5, U14.4, U14.6, U14.18, U15.4, U16.C, U$34.P$4, U$35.P$4, U$36.P$1, U$38.P$1, U$40.P$2
VCC4: C37.1, C38.A, C39.2, JP73.4, JP76.4, JP77.3, JP80.4, JP82.1, JP90.2, LED20.A, R41.2, R42.2, R50.2, SJ5.2, U17.5, U18.4, U18.6, U18.18, U19.4, U20.C, U$44.P$4, U$45.P$4, U$46.P$1, U$48.P$1, U$50.P$2
VCC5: C46.1, C47.A, C48.2, JP91.4, JP94.4, JP95.3, JP98.4, JP100.1, JP108.2, LED24.A, R51.2, R52.2, R60.2, SJ6.2, U21.5, U22.4, U22.6, U22.18, U23.4, U24.C, U$54.P$4, U$55.P$4, U$56.P$1, U$58.P$1, U$60.P$2

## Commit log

2013-03-25 Added hardware folder and included eagle files
    These initial hardware files are really "v15". They are modified from
    "v14". Modifications include moving all components to true 0603 package
    footprints. This required lots of minimal part moving and re-routing. It
    will require a new stencil.
2013-03-26 Rotated Oscillator to verticle position Had to nudge many other nearby components to make room. Also re-routed as necessary
2013-03-26 Added ingore of Eagle BRD and SCH backup files
2013-03-26 Adding Gerbers for prototype order
2013-03-26 Moved caps on FTDI Basic to avoid depanlization damage Also re-routed 5V net to more directly route to IC
2014-02-20 Updated packages on resonator, buttons and leds
2014-02-20 Switched to flags in sch, added new frame
2014-02-20 added OSHW logo
2014-02-24 Switched light sensor to ALS-PT19
2014-03-25 changed micro fiducials to regular size
2014-03-25 created panel v15
2014-08-07 Adding current files and README to repo
2014-08-07 Adding back in rev files for v15
2015-12-02 Updating README with product retired note

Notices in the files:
parts and their libraries:
SparkFun-Aesthetics: Licensing: CC v3.0 Share-Alike You are welcome to use this library for commercial purposes.
SparkFun-Sensors: Licensing: Creative Commons ShareAlike 4.0 International - https://creativecommons.org/licenses/by-sa/4.0
